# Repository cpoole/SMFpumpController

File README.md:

SMFpumpController
=================

Sustainable Microfarms Pump controller

* Boards can be assembled using the BOM and the Eagle schematic files. 
* Eagle can be downloaded for free at http://www.cadsoftusa.com/download-eagle/
* main.c is very plain and simple, it simply turns on LEDs and the pump
* the buttons still need to be debounced in software, hopefully I'll get that done shortly, if not a simple tutorial can be followed here https://www.newbiehack.com/ButtonorSwitchDebounceinSoftware.aspx 

PROGRAMMING

* follow this tutorial to setup the software http://www.ladyada.net/learn/avr/index.html
* once AVR dude is working you can program the boards with the provided makefile
* if you are using the usbtiny ISP you will need to change line 3 of the make file to reflect that
* 1st: run sudo make flash
* 2nd: run make to verify the program compiles
* 3rd: run sudo make flash to program the boards

-best of luck, Connor

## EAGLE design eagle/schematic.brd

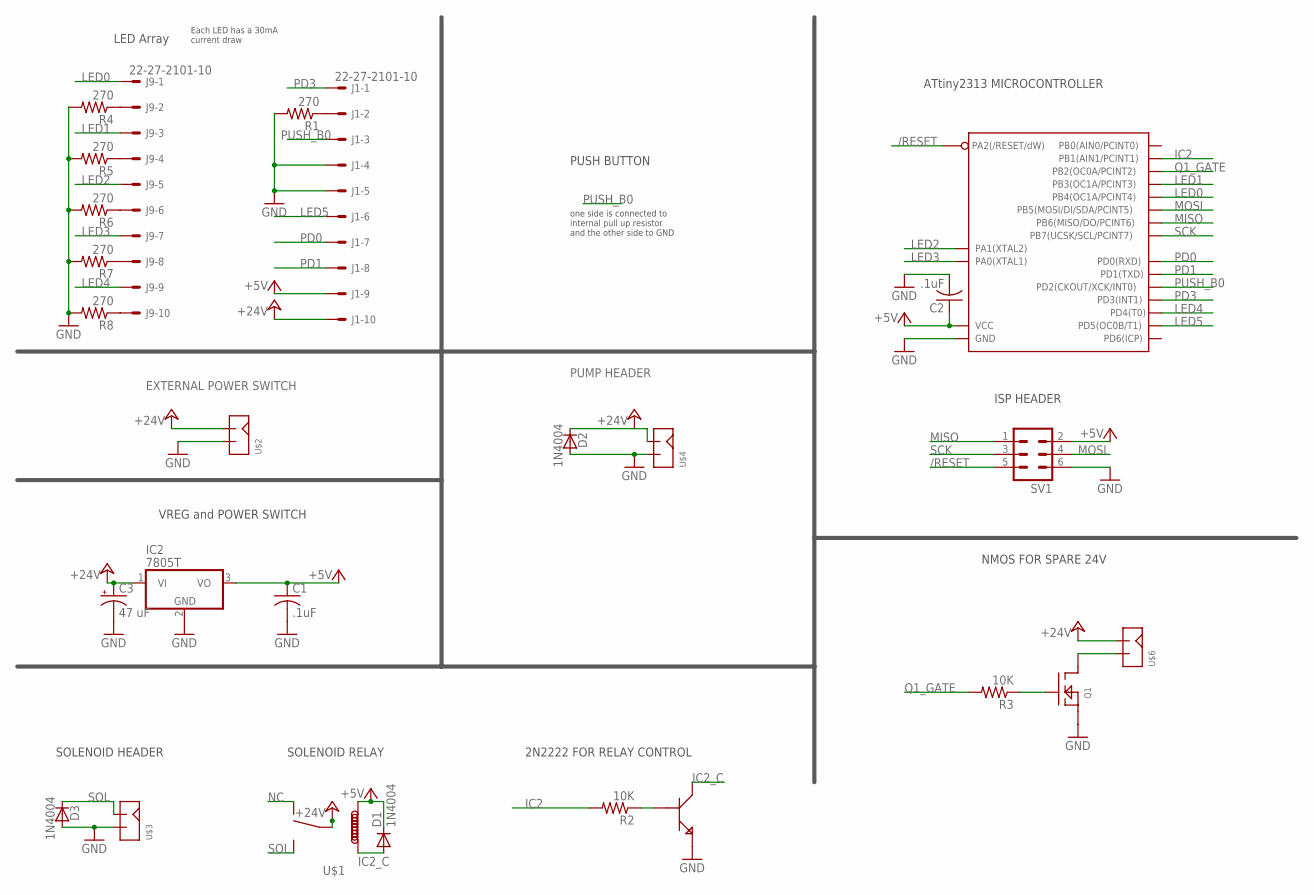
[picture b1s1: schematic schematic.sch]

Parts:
C1, C2: .1uF; C050-025X075
C3: 47 uF; B45181B
D1, D2, D3: 1N4004; DO41-10
IC2: 7805T; TO220H
J1, J9: 22-27-2101-10; 6410-10
Q1: IRLD120; HVMDIP
R1, R4, R5, R6, R7, R8: 270; 0204/7
R2, R3: 10K; 0204/7
SV1: MA03-2
U$1: JS1A-B-5V
U$2, U$3, U$4, U$6: 644752_2; 644752-2
U$5: P2N2222A
U$7: ATTINY2313; 20_DIP_MICRO

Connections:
+5V: C1.1, C2.1, D1.C, IC2.3 (VO), J1.9, SV1.2, U$1.VIN, U$7.20
+24V: C3.+, D2.C, IC2.1 (VI), J1.10, U$1.COM, U$2.PIN1, U$4.PIN1, U$6.PIN1
/RESET: SV1.5, U$7.1
GND: C1.2, C2.2, C3.-, D2.A, D3.A, IC2.2 (GND), J1.4, J1.5, Q1.S, R1.2, R4.2, R5.2, R6.2, R7.2, R8.2, SV1.6, U$2.PIN2, U$3.PIN2, U$4.PIN2, U$5.EMITTER, U$7.10
IC2: R2.2, U$7.13
IC2_C: D1.A, U$1.GND, U$5.COLLECTOR
LED0: J9.1, U$7.16
LED1: J9.3, U$7.15
LED2: J9.5, U$7.4
LED3: J9.7, U$7.5
LED4: J9.9, U$7.8
LED5: J1.6, U$7.9
MISO: SV1.1, U$7.18
MOSI: SV1.4, U$7.17
unnamed: R2.1, U$5.BASE
unnamed: Q1.G, R3.1
unnamed: J9.2, R4.1
unnamed: Q1.D, Q1.D2 (D), U$6.PIN2
unnamed: J1.2, R1.1
unnamed: J9.4, R5.1
unnamed: J9.6, R6.1
unnamed: J9.8, R7.1
unnamed: J9.10, R8.1
NC: U$1.N.C. (NC)
PD0: J1.7, U$7.2
PD1: J1.8, U$7.3
PD3: J1.1, U$7.7
PUSH_B0: J1.3, U$7.6
Q1_GATE: R3.2, U$7.14
SCK: SV1.3, U$7.19
SOL: D3.C, U$1.N.O. (NO), U$3.PIN1

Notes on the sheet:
LED Array
SOLENOID RELAY
PUSH BUTTON
VREG and POWER SWITCH
ISP HEADER
ATtiny2313 MICROCONTROLLER
2N2222 FOR RELAY CONTROL
EXTERNAL POWER SWITCH
PUMP HEADER
one side is connected to internal pull up resistor and the other side to GND
Each LED has a 30mA current draw
SOLENOID HEADER
NMOS FOR SPARE 24V

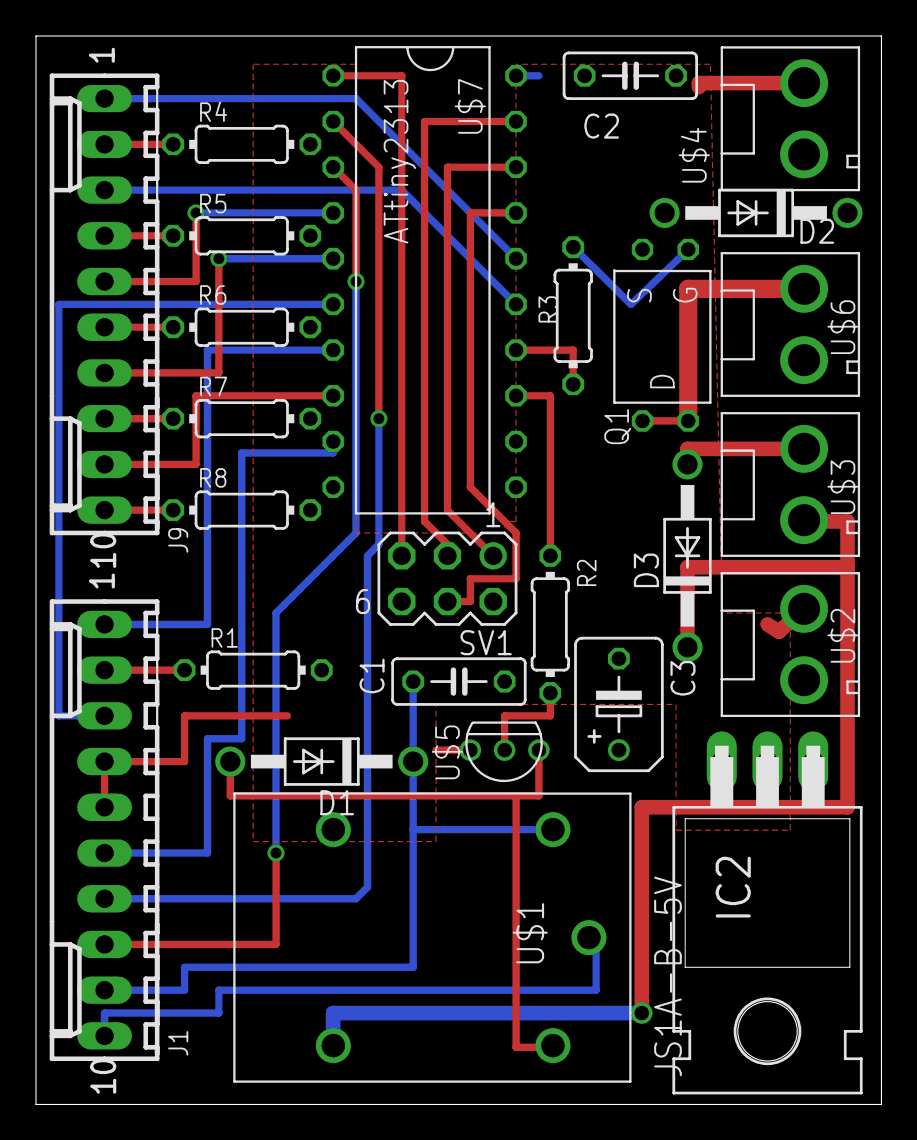
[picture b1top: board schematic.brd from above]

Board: 2 copper layers, 47.0 x 59.4 mm, 26 parts (0 on the bottom side), 30 nets.

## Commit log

2014-07-22 working mainfile
